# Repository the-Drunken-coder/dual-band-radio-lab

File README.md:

# Dual-Band Radio Lab

For the current evidence map, project boundaries and continuation state, see [project context](docs/project-context.md).

**Volunteer project:** Lane Araujo volunteered to take on this portable dual-band radio project. This repository documents the research and experiments.

## Vision

Explore a man-portable radio, roughly walkie-talkie-sized or slightly larger, with four persistent RF lanes:

- ~915 MHz LoRa
- ~915 MHz FLRC
- 2.4 GHz LoRa
- 2.4 GHz FLRC

The current architecture under evaluation gives each lane its own dedicated transceiver. Each radio normally listens continuously on its fixed network profile and may transmit on that same profile when commanded. The radios do not normally retune between bands or PHYs.

This removes the need for a separate fifth agile transmitter and also removes the requirement that all four lanes use the same radio family. Each lane can instead use hardware optimized for its own band, PHY, power, receiver performance, cost, and regulatory constraints.

The goal is to combine higher-bandwidth links with lower-rate, longer-range options for essential traffic, emergency communication, backup connectivity, and experimentation with automatic link selection. Relaying and automatic failover are possible future software features. This is the intended direction, not a demonstrated capability.

## Confirmed hardware requirements

- **U.S. operation:** Must be usable legally in the United States without an amateur-radio license.
- **Budget:** Up to $150 per complete node, with a stretch ceiling of $175.
- **Persistent receive coverage:** The node should normally monitor all four fixed network receive profiles at once rather than switching one receiver between bands or PHYs.
- **Fixed-role radios:** One transceiver is assigned to each band/PHY lane. A radio may switch between RX and TX, but does not normally change to another lane.
- **Transmission concurrency:** Simultaneous transmission on 915 MHz and 2.4 GHz is worth evaluating because the transmitters are independent. Same-band simultaneous TX/RX is not assumed to work and may require receiver blanking, filtering, protection, or additional isolation.
- **Portability:** Battery-powered and roughly walkie-talkie-sized or slightly larger. Exact dimensions, weight, and runtime are undecided.

Compute and USB/laptop connectivity remain undecided. An onboard single-board computer, such as a Raspberry Pi Zero, is an option rather than a requirement or an exclusion.

## Hardware direction

The architecture no longer requires every lane to use an LR2021. The earlier all-LR2021 design was attractive because one inexpensive chip could cover sub-GHz, 2.4 GHz, LoRa, and FLRC. With four fixed-role radios, that flexibility is no longer necessary.

Current candidate direction:

| Lane | Candidate hardware direction | Reason to investigate |
|---|---|---|
| ~915 MHz LoRa | high-power SX1262-based SPI module | mature sub-GHz LoRa hardware; 30 dBm / 1 W-capable modules exist |
| ~915 MHz FLRC | LR2021-based module | sub-GHz FLRC is an unusual LR2021 capability; high-power variants can also be evaluated |
| 2.4 GHz LoRa | high-power SX1280- or LR1121-based module | dedicated 2.4 GHz LoRa lane can prioritize link budget rather than multi-band flexibility |
| 2.4 GHz FLRC | high-power SX1280-based module or LR2021 | SX1280 is a mature 2.4 GHz FLRC/LoRa device and amplified modules exist |

These are candidates, not finalized purchases. Maximum module output power is a hardware capability, not an assumption that the maximum setting is legal for every LoRa or FLRC profile. Final frequencies, bandwidths, power, antenna gain, EIRP, and spectral limits must be validated for license-free U.S. operation before normal over-the-air testing.

When the four-lane prototype is justified, it may use four separate antennas, one per transceiver. This avoids the passive splitter loss and RF switching complexity of the earlier shared-antenna concept and makes each RF lane easier to characterize independently. Shared antennas, splitters, filters, LNAs, or duplexing can be reconsidered later if size or antenna count becomes more important.

See the [four-lane architecture](docs/dedicated-receiver-bank.md) for the long-term design and the [individual-radio test plan](docs/staged-rollout.md) for staged development of each radio.

## Develop one radio at a time

Each radio gets its own bring-up and characterization ladder: 2.4-LoRa, 2.4-FLRC, 915-LoRa and 915-FLRC. Test one lane in isolation with a compatible peer, progressing from a fixed-profile bench link through controlled tuning to its own operating envelope. Reuse a compatible SX1280 pair sequentially for the two 2.4 GHz PHYs if inventory confirms one. Combined-node and network work comes afterward.

The plan has explicit pass/stop and purchase gates. Board counts, exact variants and usable peers still need confirmation; candidates remain unselected. Do not order a full four-radio node or fabricate the [Rev A hardware](hardware/README.md) to characterize an individual radio. Its manufacturing hold remains in force.

## Optional LR2021 USB test carrier

The [dual-LR2021 USB test carrier](prototype/dual-lr2021-usb-carrier/README.md) is a separate development platform for laptop-driven radio experiments. It uses a USB-C ESP32-S3 controller and two socketed Core2021-HF-M modules. The archive includes editable KiCad files, pin maps, manufacturer evidence, validation reports, and a prototype fabrication package.

This carrier can test two chosen radio profiles at once. It does not provide the four persistent receive lanes or use the existing Rev A daughtercard interface. Firmware and the laptop test runner remain unimplemented. Physical fit, power, thermal behavior, and RF performance remain unverified.

Treat it as an optional design archive alongside the [individual-radio test plan](docs/staged-rollout.md). Its presence does not approve purchases or change the manufacturing hold on the existing [Rev A hardware](hardware/README.md).

## Example deployment

A person inside a house connects through a rooftop relay to a drone roughly one mile away. Every node normally keeps the four standardized receive profiles active. For outgoing traffic, the host selects the appropriate lane and that lane's transceiver temporarily changes from RX to TX.

A transmission on one band may require the other receiver on that same band to be blanked or protected from local transmitter leakage. Opposite-band receivers may be able to continue receiving during transmission, and simultaneous 915 MHz plus 2.4 GHz transmission is an experiment enabled by the independent radios rather than a guaranteed capability.

This is a scenario to test, not a confirmed range claim or a commitment to specific relaying or failover software. Terrain or obstructions could interrupt multiple links; 915 MHz is not assumed to guarantee coverage behind a hill.

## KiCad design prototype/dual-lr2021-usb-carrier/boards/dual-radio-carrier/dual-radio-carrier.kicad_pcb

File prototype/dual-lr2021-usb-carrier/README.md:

# Dual-LR2021 USB test carrier

A socketed, laptop-powered test platform for two Waveshare Core2021-HF-M radio modules. An ESP32-S3 controller handles the radios. The carrier replaces breadboard jumper wires with PCB traces and female sockets.

The intended workflow is to plug in USB-C, flash firmware from the laptop, command repeatable experiments, and collect machine-readable results. AI coding agents can use the same command-line tools as a person. The firmware and laptop test runner have not been implemented.

## Place in Dual-Band Radio Lab

This is an optional LR2021 development platform. It can help characterize individual LR2021 links and, later, interactions between two radios. Two copies provide two test nodes, each with two radios.

The project's [four-lane architecture](../../docs/dedicated-receiver-bank.md) requires four radios to monitor four persistent network profiles. This carrier holds two radios and can monitor two selected profiles at once. Changing their configuration between experiments does not provide four simultaneous listeners.

The existing [Rev A hardware](../../hardware/README.md) is a separate Pico 2 carrier with E22, Core2021, and E28 daughtercards. This ESP32 carrier uses direct Core2021 sockets. The controllers, GPIO maps, power arrangements, and card interfaces differ. The other daughtercards do not plug into this carrier.

The [individual-radio test plan](../../docs/staged-rollout.md) remains the development sequence. Existing-radio tests do not require this PCB. Adding this archive does not select LR2021 for every lane, approve purchases, or release the existing Rev A hardware for manufacturing.

## System

```mermaid
flowchart TD
    Host["Laptop: flash tools and future test runner"] -->|USB-C data| Bridge["Controller USB hub and CH343 serial bridge"]
    Bridge -->|UART and automatic BOOT/reset| MCU["ESP32-S3 firmware"]
    MCU -->|Shared SPI and separate CS, IRQ, BUSY, RESET| A["Core2021 radio A"]
    MCU -->|Shared SPI and separate CS, IRQ, BUSY, RESET| B["Core2021 radio B"]
    Host -->|USB power| Input["Controller USB supply and D1 diode"]
    Input --> LDO["Carrier 3.3 V radio regulator"]
    LDO --> A
    LDO --> B
    A --> AntA["Module antenna ports"]
    B --> AntB["Module antenna ports"]
```

Either radio can use a supported LoRa or FLRC profile at 915 MHz or 2.4 GHz. Firmware assigns each radio's role. One radio transmits or receives on its selected profile at a time. Nearby operation of both radios requires RF coupling and coexistence measurements.

The carrier routes digital signals and power. RF stays on the modules and their antenna connectors. There is no carrier RF switch, filter, or receiver-protection network. There is no battery input.

See [system responsibilities and intended software](SYSTEM.md) for the control flow, recovery behavior, and unfinished work.

## Hardware and files

The PCB is 100 x 75 mm, two layers, and 1.6 mm thick. Female sockets, the regulator, resistors, and capacitors are soldered to the carrier. The controller and radios plug in afterward.

| Item | Per carrier |
| --- | ---: |
| Waveshare ESP32-S3-DEV-KIT-N8R8-M, SKU 24243 | 1 |
| Waveshare Core2021-HF-M, SKU 34523 | 2 |
| Samtec SSW-122-01-G-S controller sockets | 2 |
| Samtec SSW-108-01-G-S radio sockets | 4 |
| TI TLV1117LV33DCYR radio regulator | 1 |

The [BOM](boards/dual-radio-carrier/bom.csv) includes the remaining parts and separately purchased plug-in modules. Antennas, USB cables, and mounting hardware are not included. Use the exact selected module variants and check their supplied male headers against socket samples.

- [Editable KiCad project](boards/dual-radio-carrier/dual-radio-carrier.kicad_pro), [PCB](boards/dual-radio-carrier/dual-radio-carrier.kicad_pcb), and [schematic](boards/dual-radio-carrier/dual-radio-carrier.kicad_sch).
- [Assembly, GPIO, power, and rebuild instructions](boards/dual-radio-carrier/README.md).
- [GPIO map](boards/dual-radio-carrier/gpio-map.csv) and [radio socket map](boards/dual-radio-carrier/radio-socket-map.csv).
- [Native KiCad check summary](boards/dual-radio-carrier/build/native-summary.json) and [saved-file geometry checks](boards/dual-radio-carrier/build/verification.json).
- [Archived manufacturer evidence](extra/references/) and [historical independent review](extra/reviews/electrical-review.md).
- [Prototype Gerber, drill, BOM, and placement package](mfg/dual-radio-carrier-rev-a-prototype.zip), with [source and output hashes](mfg/dual-radio-carrier-rev-a-prototype/manifest.json).

## Validation and manufacturing status

Native KiCad 10.99.0 checks passed on the saved files: zero ERC violations, zero DRC violations, zero unconnected items, and zero schematic parity issues. The separate saved-file checker also passed. Report hashes identify the exact PCB and schematic in this archive.

No physical board has been fabricated, assembled, or tested. These results do not establish socket fit, USB power capacity, temperature, flashing reliability, or RF performance. The controller's external header current allowance is not specified by its manufacturer. The radio regulator's rating does not establish the upstream USB or diode capacity.

The manufacturing files are an engineering-prototype snapshot for review, not evidence of manufacturing approval or supplier acceptance. No quote, order, manufacturer upload, or purchase has been made. The generic BOM includes plug-in modules, while placement data contains only carrier-mounted parts. A factory assembly handoff must separate those items and confirm part sourcing, through-hole assembly, orientation, and coordinate conventions with the chosen supplier.

The first assembled units need sample-fit, power, thermal, USB recovery, and controlled radio tests. Keep the project's existing manufacturing hold and staged purchase decisions separate from this archive.

## Working with this snapshot

Open the KiCad project inside `boards/dual-radio-carrier/`. The checked board uses the native file format saved by Backplane KiCad 10.99.0. Do not assume older stable KiCad releases can open it.

Run the existing rebuild instructions from this directory:

```sh
cd prototype/dual-lr2021-usb-carrier
```

Generators can overwrite manual CAD edits. Preserve the included final PCB and schematic before regeneration. The saved native CAD files are the uploaded design, and the build reports apply only while their hashes match.

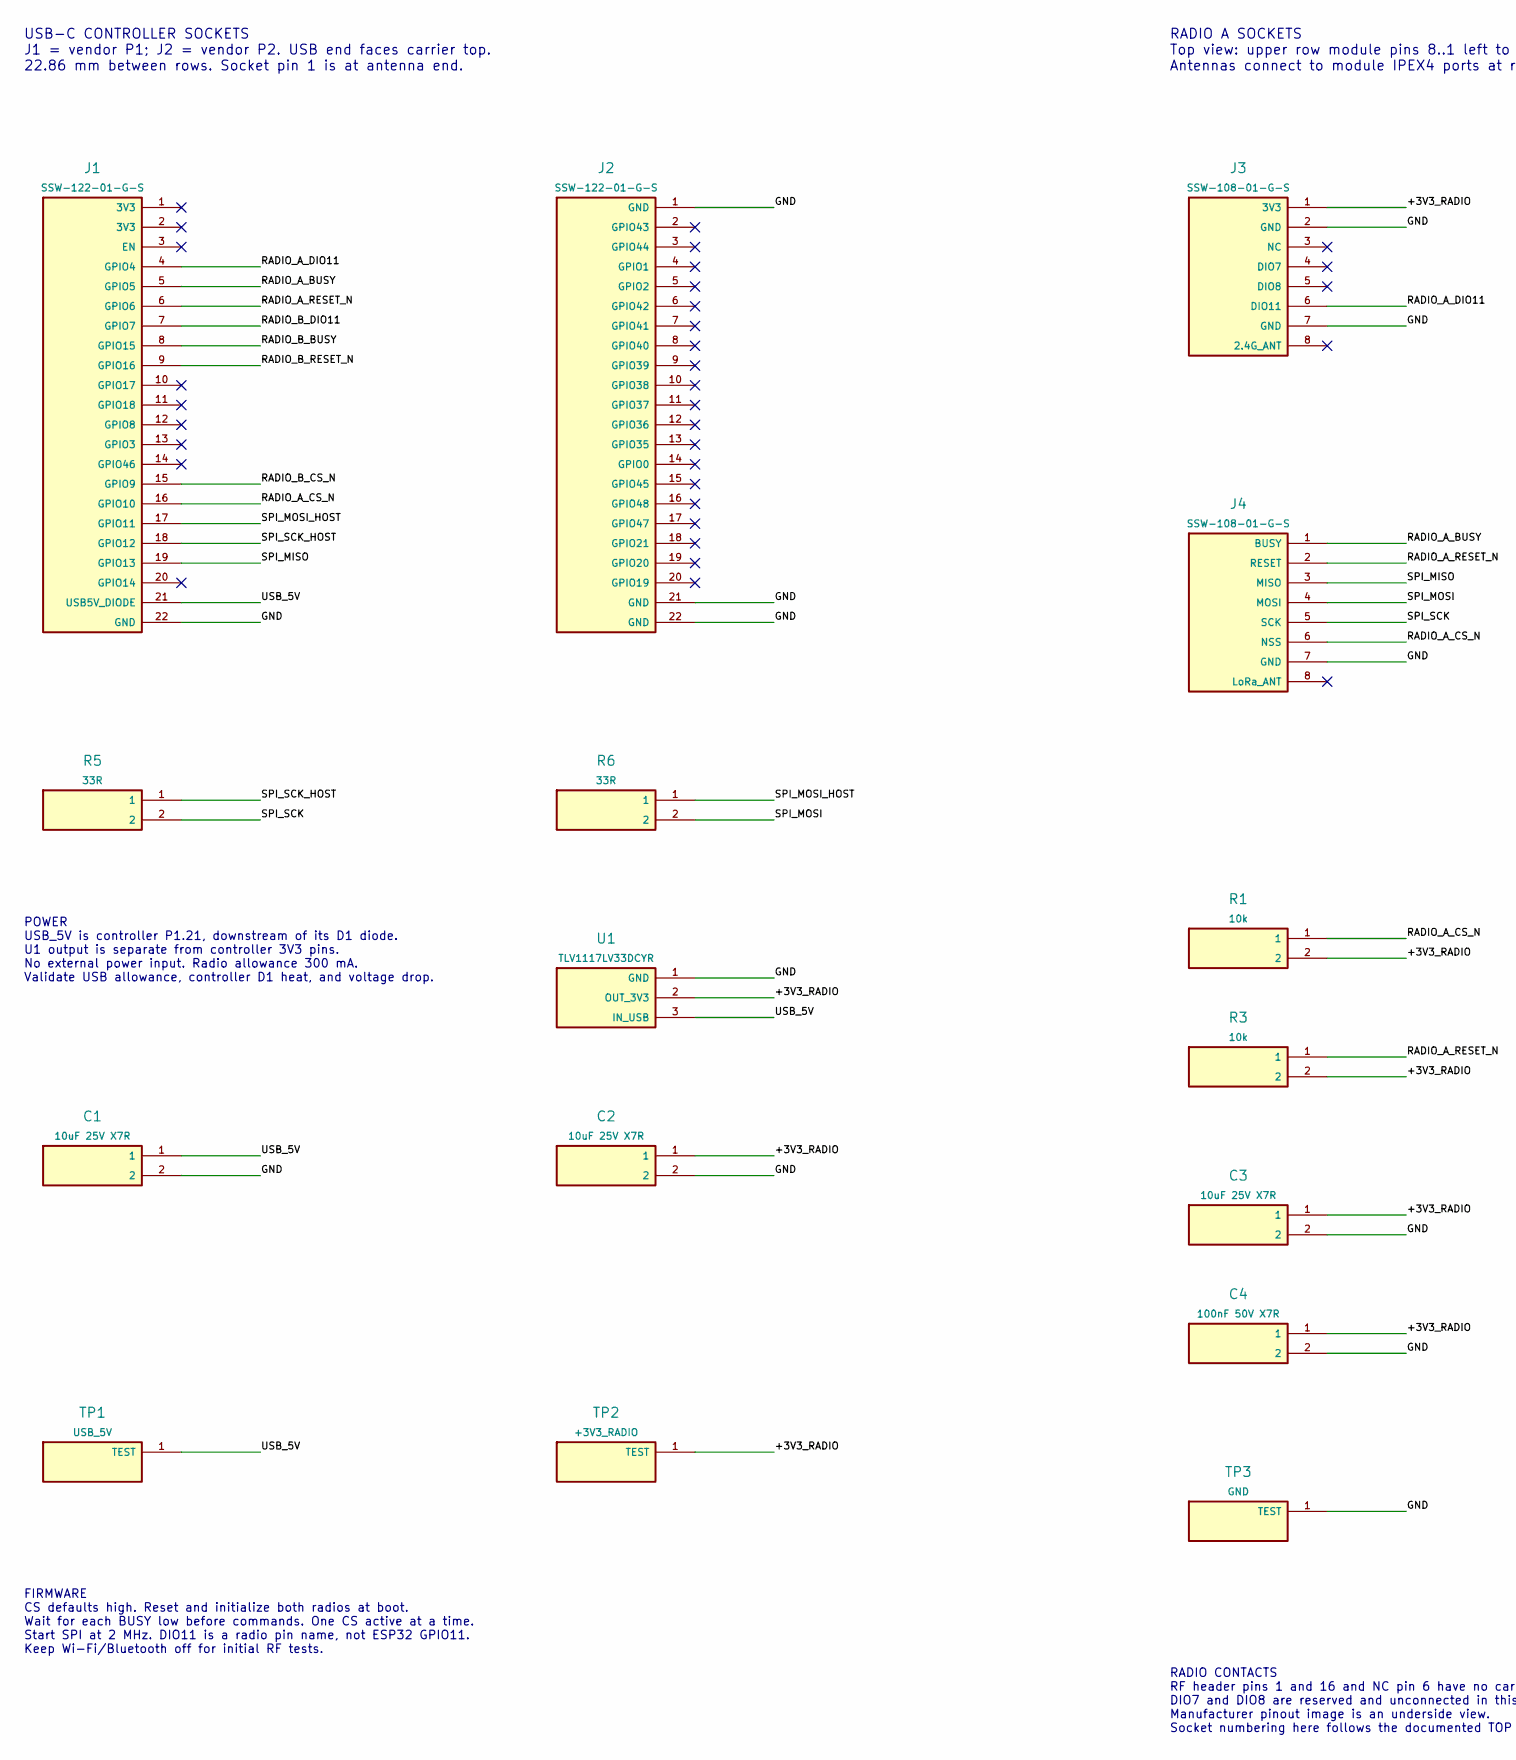
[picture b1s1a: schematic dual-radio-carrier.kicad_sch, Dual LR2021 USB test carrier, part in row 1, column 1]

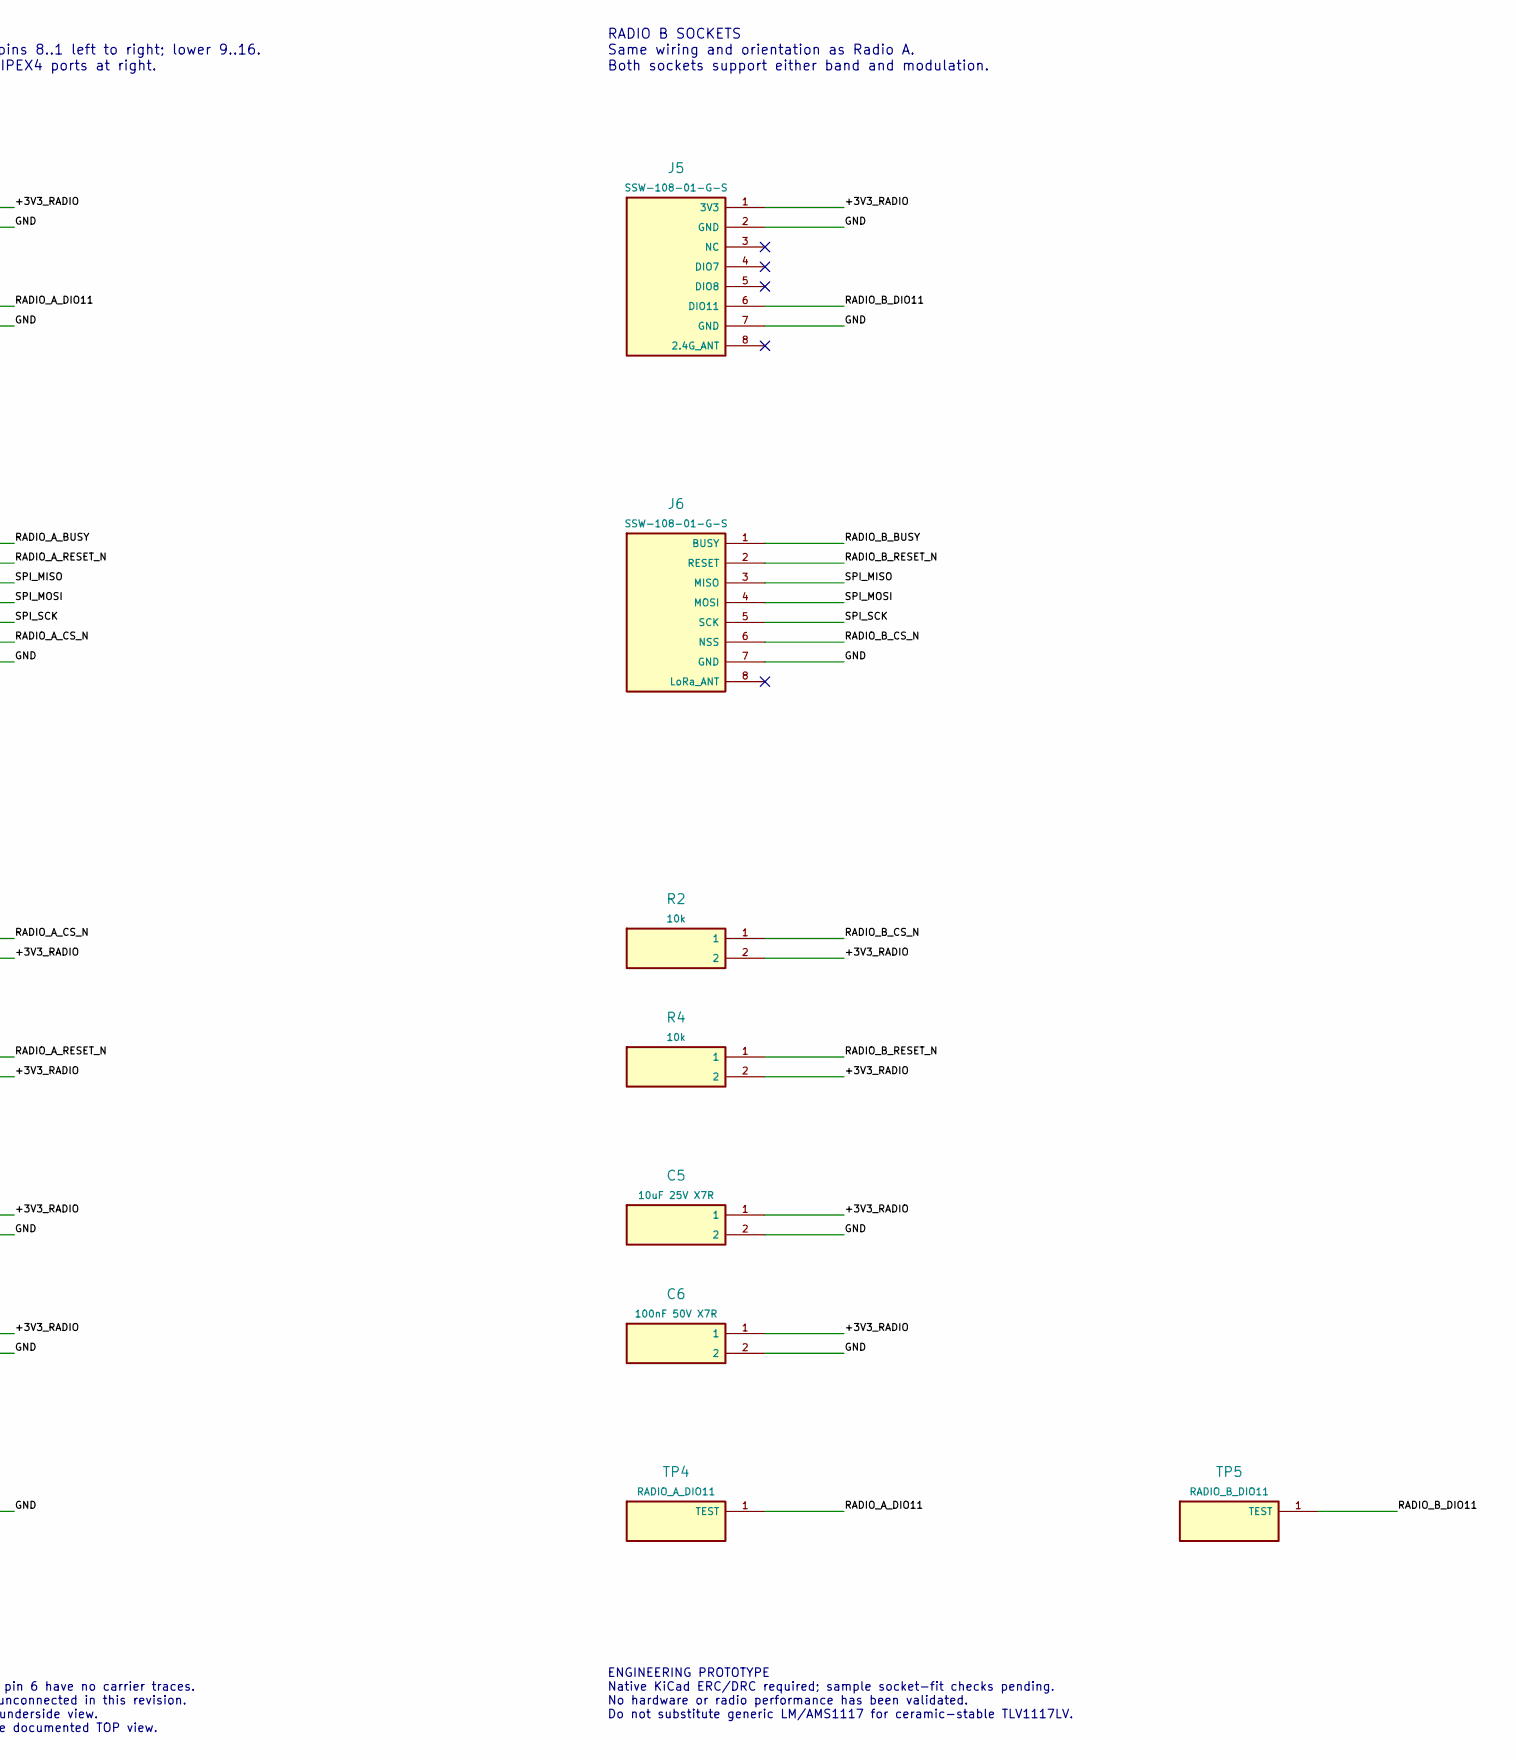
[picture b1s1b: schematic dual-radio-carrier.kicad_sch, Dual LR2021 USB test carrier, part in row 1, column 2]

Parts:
C1, C2, C3, C5: 10uF 25V X7R; C_1206; MPN C1206C106K3RACTU
C4, C6: 100nF 50V X7R; C_0805; MPN C0805C104K5RACTU
J1, J2: SSW-122-01-G-S; Socket_1x22_P2.54_USB_Top; MPN SSW-122-01-G-S
J3: SSW-108-01-G-S; Socket_1x08_P2.54_Horizontal_SolidGND2; MPN SSW-108-01-G-S
J4, J5, J6: SSW-108-01-G-S; Socket_1x08_P2.54_Horizontal; MPN SSW-108-01-G-S
R1, R2, R3, R4: 10k; R_0805; MPN RC0805FR-0710KL
R5, R6: 33R; R_0805; MPN RC0805FR-0733RL
TP1: USB_5V; TestPoint_1.5mm; MPN PCB copper test pad
TP2: +3V3_RADIO; TestPoint_1.5mm; MPN PCB copper test pad
TP3: GND; TestPoint_1.5mm; MPN PCB copper test pad
TP4: RADIO_A_DIO11; TestPoint_1.5mm; MPN PCB copper test pad
TP5: RADIO_B_DIO11; TestPoint_1.5mm; MPN PCB copper test pad
U1: TLV1117LV33DCYR; SOT223_TabPin2; MPN TLV1117LV33DCYR

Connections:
/+3V3_RADIO: C2.1, C3.1, C4.1, C5.1, C6.1, J3.1 (3V3), J5.1 (3V3), R1.2, R2.2, R3.2, R4.2, TP2.1, U1.2 (OUT_3V3)
/GND: C1.2, C2.2, C3.2, C4.2, C5.2, C6.2, J1.22 (GND), J2.1 (GND), J2.21 (GND), J2.22 (GND), J3.2 (GND), J3.7 (GND), J4.7 (GND), J5.2 (GND), J5.7 (GND), J6.7 (GND), TP3.1, U1.1 (GND)
/RADIO_A_BUSY: J1.5 (GPIO5), J4.1 (BUSY)
/RADIO_A_CS_N: J1.16 (GPIO10), J4.6 (NSS), R1.1
/RADIO_A_DIO11: J1.4 (GPIO4), J3.6 (DIO11), TP4.1
/RADIO_A_RESET_N: J1.6 (GPIO6), J4.2 (RESET), R3.1
/RADIO_B_BUSY: J1.8 (GPIO15), J6.1 (BUSY)
/RADIO_B_CS_N: J1.15 (GPIO9), J6.6 (NSS), R2.1
/RADIO_B_DIO11: J1.7 (GPIO7), J5.6 (DIO11), TP5.1
/RADIO_B_RESET_N: J1.9 (GPIO16), J6.2 (RESET), R4.1
/SPI_MISO: J1.19 (GPIO13), J4.3 (MISO), J6.3 (MISO)
/SPI_MOSI: J4.4 (MOSI), J6.4 (MOSI), R6.2
/SPI_MOSI_HOST: J1.17 (GPIO11), R6.1
/SPI_SCK: J4.5 (SCK), J6.5 (SCK), R5.2
/SPI_SCK_HOST: J1.18 (GPIO12), R5.1
/USB_5V: C1.1, J1.21 (USB5V_DIODE), TP1.1, U1.3 (IN_USB)

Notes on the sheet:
USB-C CONTROLLER SOCKETS J1 = vendor P1; J2 = vendor P2. USB end faces carrier top. 22.86 mm between rows. Socket pin 1 is at antenna end.
RADIO A SOCKETS Top view: upper row module pins 8..1 left to right; lower 9..16. Antennas connect to module IPEX4 ports at right.
RADIO B SOCKETS Same wiring and orientation as Radio A. Both sockets support either band and modulation.
POWER USB_5V is controller P1.21, downstream of its D1 diode. U1 output is separate from controller 3V3 pins. No external power input. Radio allowance 300 mA. Validate USB allowance, controller D1 heat, and voltage drop.
FIRMWARE CS defaults high. Reset and initialize both radios at boot. Wait for each BUSY low before commands. One CS active at a time. Start SPI at 2 MHz. DIO11 is a radio pin name, not ESP32 GPIO11. Keep Wi-Fi/Bluetooth off for initial RF tests.
RADIO CONTACTS RF header pins 1 and 16 and NC pin 6 have no carrier traces. DIO7 and DIO8 are reserved and unconnected in this revision. Manufacturer pinout image is an underside view. Socket numbering here follows the documented TOP view.
ENGINEERING PROTOTYPE Native KiCad ERC/DRC required; sample socket-fit checks pending. No hardware or radio performance has been validated. Do not substitute generic LM/AMS1117 for ceramic-stable TLV1117LV.

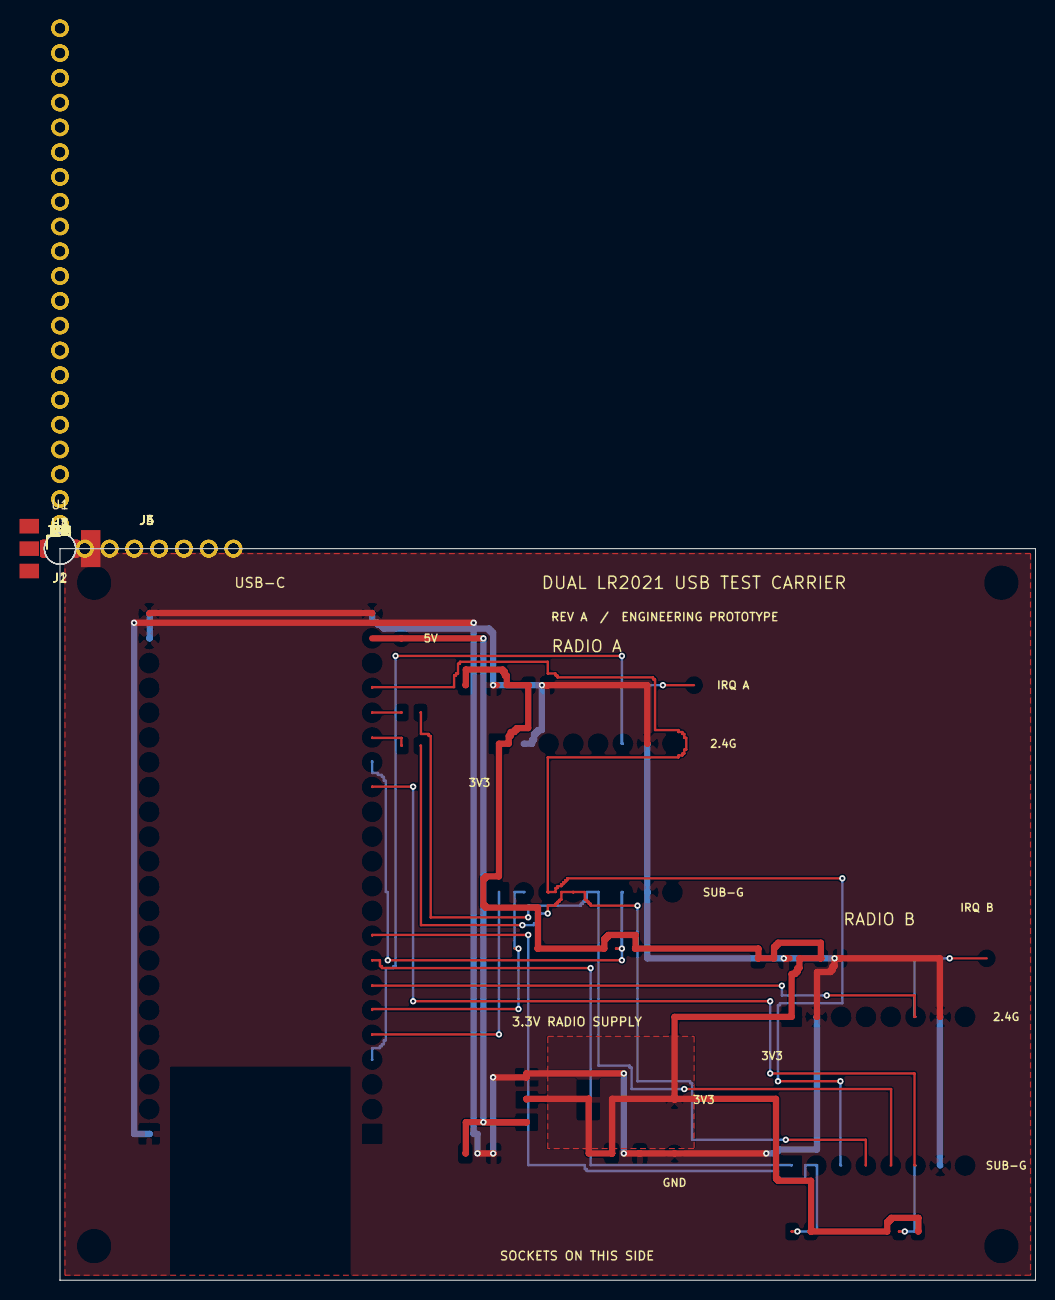
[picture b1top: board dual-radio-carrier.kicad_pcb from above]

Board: 2 copper layers, 100.0 x 75.0 mm, 28 parts (0 on the bottom side), 16 nets.

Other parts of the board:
H1, H2, H3, H4: M3 NPTH; MountingHole_3.2mm

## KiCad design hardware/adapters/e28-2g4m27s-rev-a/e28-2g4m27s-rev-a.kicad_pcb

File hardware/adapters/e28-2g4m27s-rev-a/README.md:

# e28-2g4m27s-rev-a

Editable Rev A schematic, routed PCB, selected BOM and schematic PDF. Native KiCad ERC and DRC pass with zero findings, including schematic parity. Two layers, 2 oz copper per side. Review only; no manufacturing release.

Open [e28-2g4m27s-rev-a.kicad_pcb](e28-2g4m27s-rev-a.kicad_pcb) in KiCad. The final native board is authoritative; do not overwrite it with the intermediate router session. See the hardware DESIGN_REVIEW.md, POWER_BUDGET.md and ASSEMBLY_NOTES.md for access, route lengths, power estimates and later physical acceptance.

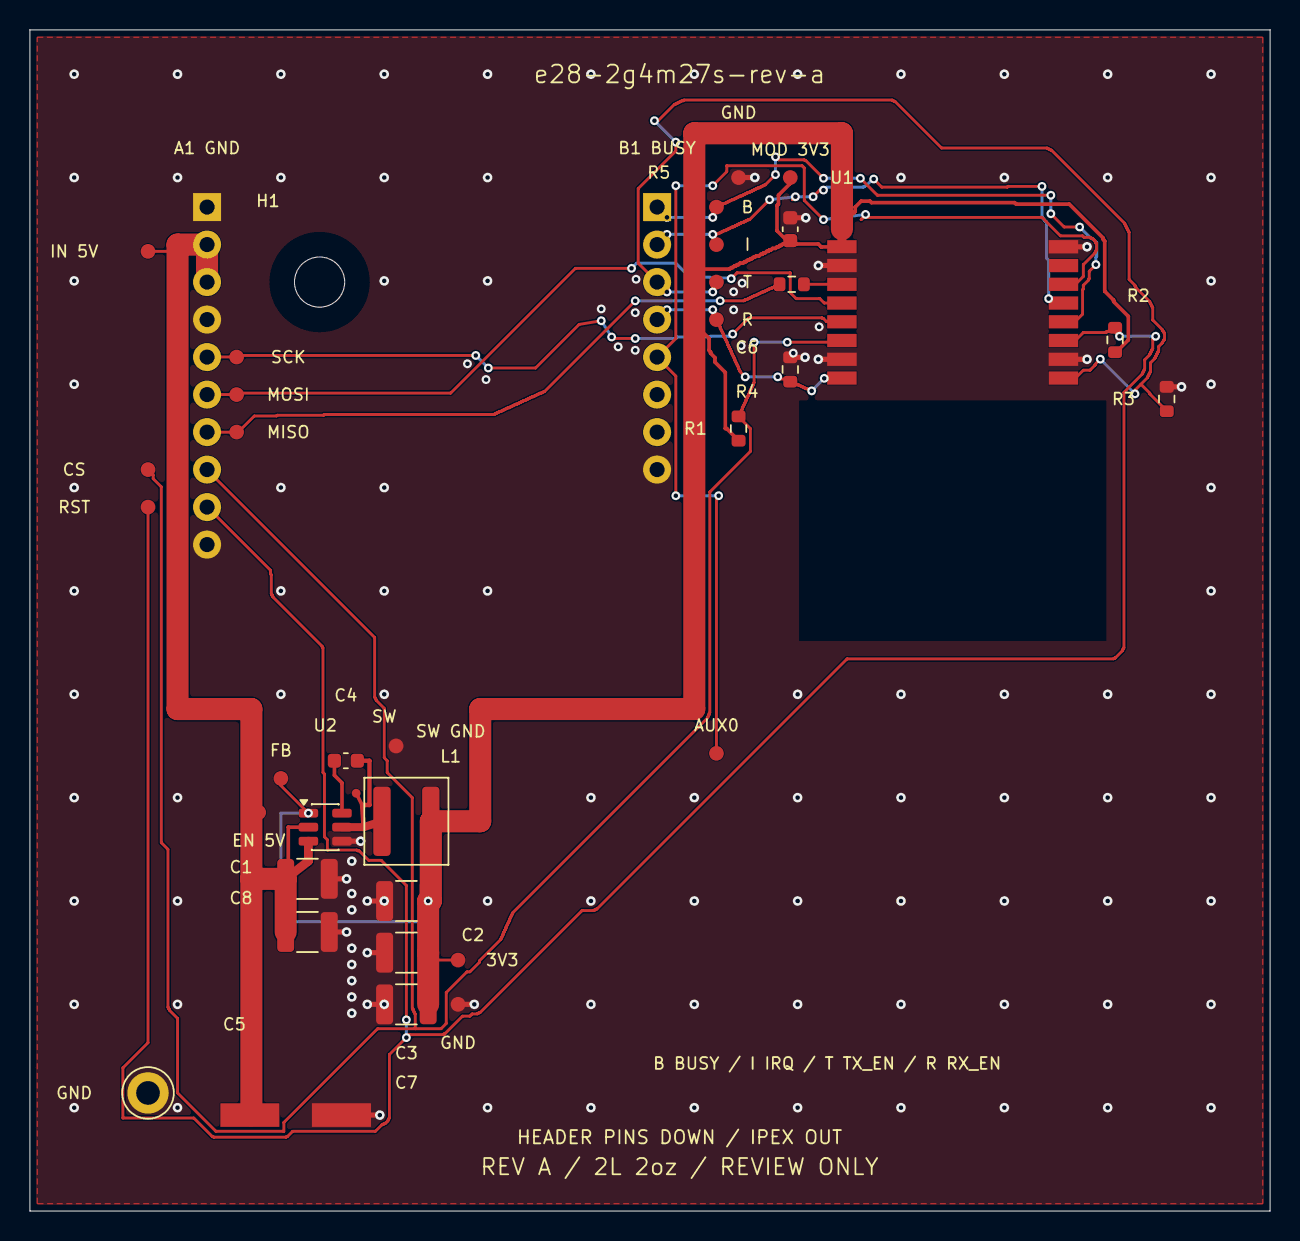
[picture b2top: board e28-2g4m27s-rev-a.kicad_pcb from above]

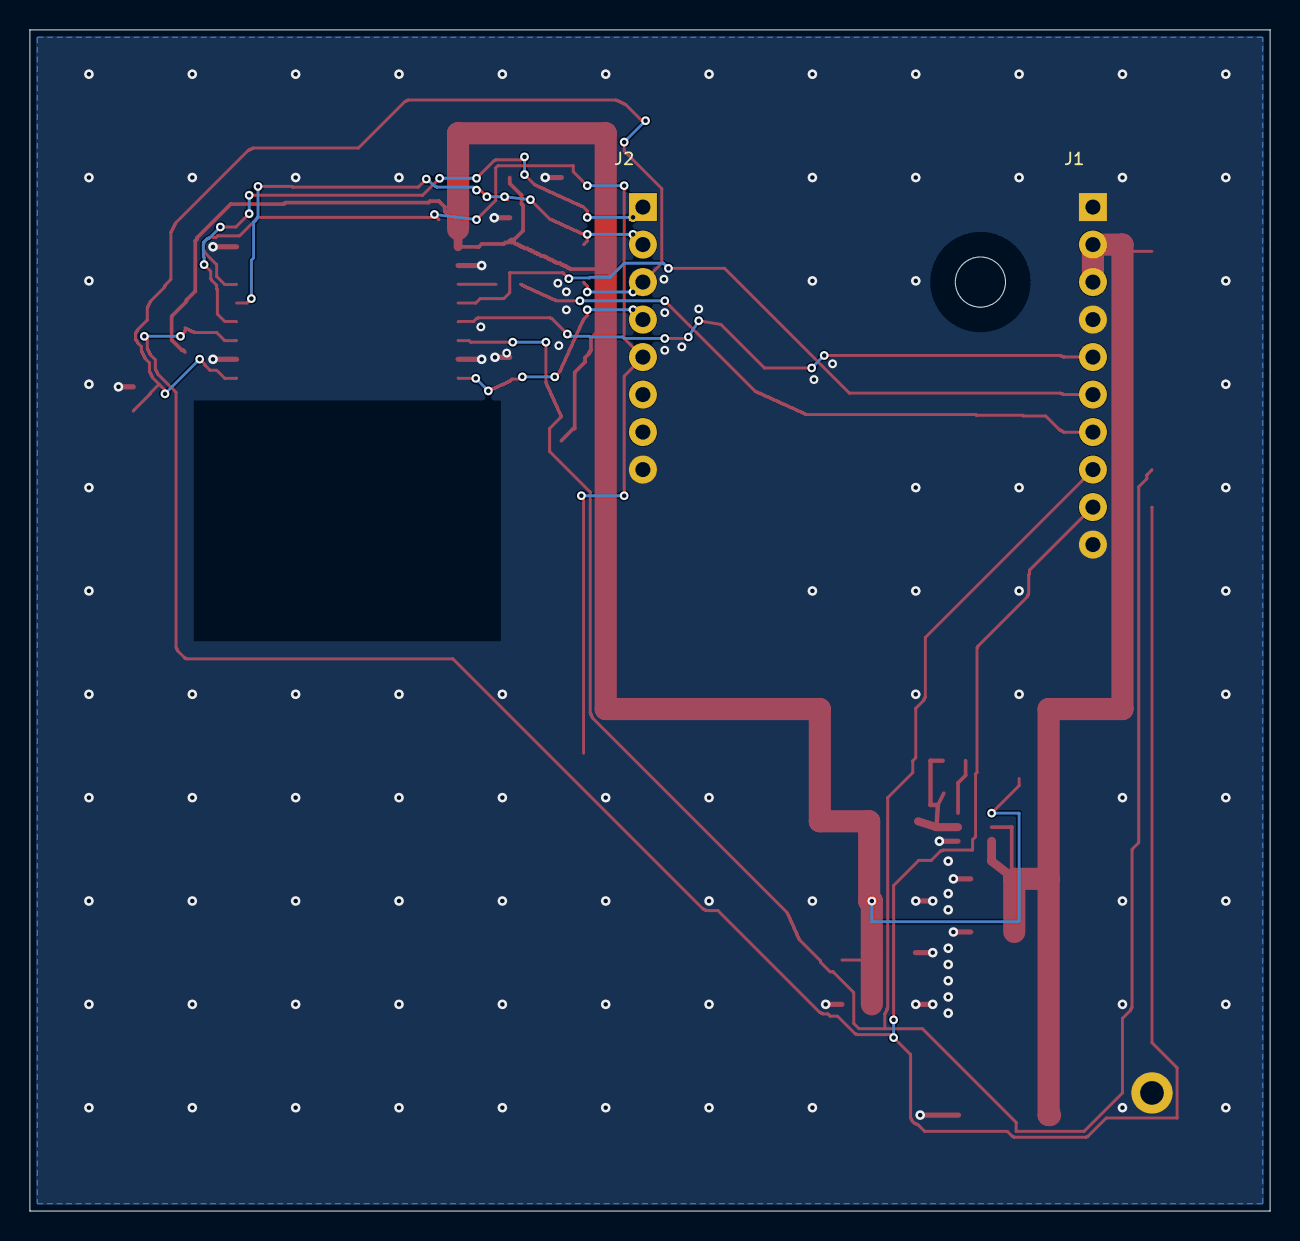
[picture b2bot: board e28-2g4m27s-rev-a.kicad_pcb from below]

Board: 2 copper layers, 84.0 x 80.0 mm, 39 parts (2 on the bottom side), 16 nets.

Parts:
C1, C2, C3, C7, C8: 22uF; C_1210_3225Metric
C4, C6: 100nF; C_0603_1608Metric
C5: 220uF; Panasonic_FK_E_8x6.2
H1: M3 alignment hole; Alignment_M3_3.4mm
J1: TSW-110-07-G-S; TSW_1x10
J2: TSW-108-07-G-S; TSW_1x8
L1: 4.7uH; L_Coilcraft_XAL5030-XXX
R1, R2, R3, R4: 10k; R_0603_1608Metric
R5: 22; R_0603_1608Metric
TP1: SPI_SCK; Probe_Pad_D1.0mm
TP2: SPI_MOSI; Probe_Pad_D1.0mm
TP3: SPI_MISO; Probe_Pad_D1.0mm
TP4: CS_N; Probe_Pad_D1.0mm
TP5: RESET_N; Probe_Pad_D1.0mm
TP6: BUSY; Probe_Pad_D1.0mm
TP7: IRQ; Probe_Pad_D1.0mm
TP8: TX_EN; Probe_Pad_D1.0mm
TP9: RX_EN; Probe_Pad_D1.0mm
TP10: IN_5V; Probe_Pad_D1.0mm
TP11: CLIP_GND; TestPoint_Keystone_5010-5014_Multipurpose
TP12: AUX0; Probe_Pad_D1.0mm
TP13: OUT_3V3; Probe_Pad_D1.0mm
TP14: REG_GND; Probe_Pad_D1.0mm
TP15: EN_5V; Probe_Pad_D1.0mm
TP16: SW; Probe_Pad_D0.6mm
TP17: FB; Probe_Pad_D1.0mm
TP18: MOD_3V3; Probe_Pad_D1.0mm
TP19: MOD_GND; Probe_Pad_D1.0mm
TP20: SW_GND; Probe_Pad_D1.0mm
U1: E28-2G4M27S; E28_2G4M27S
U2: AP63203WU-7; TSOT-23-6

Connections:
/AUX0: J2.5, TP12.1, U1.14
/BST: C4.1, U2.6
/BUSY: J2.1, TP6.1, U1.12
/CS_N: J1.8, R1.2, TP4.1, U1.6
/GND: C1.2, C2.2, C3.2, C5.2, C6.2, C7.2, C8.2, J1.1, J1.4, J1.10, J2.8, R3.2, R4.2, TP11.1, TP14.1, TP19.1, TP20.1, U1.2, U1.7, U1.10, U1.16, U2.4
/IRQ: J2.2, TP7.1, U1.13
/RADIO_3V3: C2.1, C3.1, C6.1, C7.1, L1.2, R1.1, R2.1, TP13.1, TP17.1, TP18.1, U1.1, U2.1
/RESET_N: J1.9, R2.2, TP5.1, U1.11
/RX_EN: J2.4, R4.1, TP9.1, U1.8
/SLOT_5V: C1.1, C5.1, C8.1, J1.2, J1.3, TP10.1, TP15.1, U2.2, U2.3
/SPI_MISO: J1.7, R5.2, TP3.1
/SPI_MISO_SRC: R5.1, U1.3
/SPI_MOSI: J1.6, TP2.1, U1.4
/SPI_SCK: J1.5, TP1.1, U1.5
/SW: C4.2, L1.1, TP16.1, U2.5
/TX_EN: J2.3, R3.1, TP8.1, U1.9

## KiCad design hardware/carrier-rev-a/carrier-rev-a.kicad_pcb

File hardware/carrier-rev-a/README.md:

# carrier-rev-a

Editable Rev A schematic, routed PCB, selected BOM and schematic PDF. Native KiCad ERC and DRC pass with zero findings, including schematic parity. Two layers, 2 oz copper per side. Review only; no manufacturing release.

Open [carrier-rev-a.kicad_pcb](carrier-rev-a.kicad_pcb) in KiCad. The final native board is authoritative; do not overwrite it with the intermediate router session. See the hardware DESIGN_REVIEW.md, POWER_BUDGET.md and ASSEMBLY_NOTES.md for access, route lengths, power estimates and later physical acceptance.

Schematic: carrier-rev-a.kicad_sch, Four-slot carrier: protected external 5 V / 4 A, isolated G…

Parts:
C1: 10nF; C_0603_1608Metric; MPN GRM188R71H103KA01D
C2: 1uF; C_0805_2012Metric; MPN GRM21BR71C105KA01L
C3: 220uF; Panasonic_FK_E_8x6.2; MPN EEEFK1A221P
C4, C5: 22uF; C_1210_3225Metric; MPN C3225X7R1E226M250AB
C6, C7, C8, C9, C10, C11, C12: 100nF; C_0603_1608Metric; MPN GRM188R71H104KA93D
H1, H2, H3, H4: Captive M3 x 25 alignment post; Alignment_M3_3.4mm; MPN SSCF-M3-25-A2
J1, J3, J5, J7: SSQ-110-01-G-S; SSQ_1x10; MPN SSQ-110-01-G-S
J2, J4, J6, J8: SSQ-108-01-G-S; SSQ_1x8; MPN SSQ-108-01-G-S
J9: 5 V / 4 A INPUT; PhoenixContact_MSTBA_2,5_2-G-5,08_1x02_P5.08mm_Horizontal; MPN 1757242
J10, J11: SSQ-120-01-G-S; SSQ_1x20; MPN SSQ-120-01-G-S
MP1, MP2, MP3, MP4: M3 captive-post clamp nut; MPN HPN-M3-A2
MP5: External cable mating plug; MPN 1757019
Q1: DMG2305UX-7; SOT-23; MPN DMG2305UX-7
R1: 267k; R_0603_1608Metric; MPN RC0603FR-07267KL
R2, R7, R10: 100k; R_0603_1608Metric; MPN RC0603FR-07100KL
R3: 340k 0.1%; R_0603_1608Metric; MPN RT0603BRD07340KL
R4: 100k 0.1%; R_0603_1608Metric; MPN RT0603BRD07100KL
R5: 715; R_0603_1608Metric; MPN RC0603FR-07715RL
R6, R8, R9, R13, R14, R15, R16, R17, R18: 10k; R_0603_1608Metric; MPN RC0603FR-0710KL
R11, R12: 1k; R_0603_1608Metric; MPN RC0603FR-071KL
R19: 100; R_0603_1608Metric; MPN RC0603FR-07100RL
R20, R21, R22: 22; R_0603_1608Metric; MPN RC0603FR-0722RL
TP1: S1_5V; Probe_Pad_D1.0mm; MPN PCB-PROBE-PAD
TP2: S1_CS_N; Probe_Pad_D1.0mm; MPN PCB-PROBE-PAD
TP3: S1_BUSY; Probe_Pad_D1.0mm; MPN PCB-PROBE-PAD
TP4: S1_IRQ; Probe_Pad_D1.0mm; MPN PCB-PROBE-PAD
TP5: S1_RESET_N; Probe_Pad_D1.0mm; MPN PCB-PROBE-PAD
TP6: S1_TX_EN; Probe_Pad_D1.0mm; MPN PCB-PROBE-PAD
TP7: S1_RX_EN; Probe_Pad_D1.0mm; MPN PCB-PROBE-PAD
TP8: S1_GND; TestPoint_Keystone_5010-5014_Multipurpose; MPN 5011
TP9: S2_5V; Probe_Pad_D1.0mm; MPN PCB-PROBE-PAD
TP10: S2_CS_N; Probe_Pad_D1.0mm; MPN PCB-PROBE-PAD
TP11: S2_BUSY; Probe_Pad_D1.0mm; MPN PCB-PROBE-PAD
TP12: S2_IRQ; Probe_Pad_D1.0mm; MPN PCB-PROBE-PAD
TP13: S2_RESET_N; Probe_Pad_D1.0mm; MPN PCB-PROBE-PAD
TP14: S2_GND; TestPoint_Keystone_5010-5014_Multipurpose; MPN 5011
TP15: S3_5V; Probe_Pad_D1.0mm; MPN PCB-PROBE-PAD
TP16: S3_CS_N; Probe_Pad_D1.0mm; MPN PCB-PROBE-PAD
TP17: S3_BUSY; Probe_Pad_D1.0mm; MPN PCB-PROBE-PAD
TP18: S3_IRQ; Probe_Pad_D1.0mm; MPN PCB-PROBE-PAD
TP19: S3_RESET_N; Probe_Pad_D1.0mm; MPN PCB-PROBE-PAD
TP20: S3_TX_EN; Probe_Pad_D1.0mm; MPN PCB-PROBE-PAD
TP21: S3_RX_EN; Probe_Pad_D1.0mm; MPN PCB-PROBE-PAD
TP22: S3_GND; TestPoint_Keystone_5010-5014_Multipurpose; MPN 5011
TP23: S4_5V; Probe_Pad_D1.0mm; MPN PCB-PROBE-PAD
TP24: S4_CS_N; Probe_Pad_D1.0mm; MPN PCB-PROBE-PAD
TP25: S4_BUSY; Probe_Pad_D1.0mm; MPN PCB-PROBE-PAD
TP26: S4_IRQ; Probe_Pad_D1.0mm; MPN PCB-PROBE-PAD
TP27: S4_RESET_N; Probe_Pad_D1.0mm; MPN PCB-PROBE-PAD
TP28: S4_TX_EN; Probe_Pad_D1.0mm; MPN PCB-PROBE-PAD
TP29: S4_RX_EN; Probe_Pad_D1.0mm; MPN PCB-PROBE-PAD
TP30: S4_GND; TestPoint_Keystone_5010-5014_Multipurpose; MPN 5011
TP31: IN_5V; Probe_Pad_D1.0mm; MPN PCB-PROBE-PAD
TP32: BUS_5V; Probe_Pad_D1.0mm; MPN PCB-PROBE-PAD
TP33: VBUS; Probe_Pad_D1.0mm; MPN PCB-PROBE-PAD
TP34: VSYS; Probe_Pad_D1.0mm; MPN PCB-PROBE-PAD
TP35: PICO_3V3; Probe_Pad_D1.0mm; MPN PCB-PROBE-PAD
TP36: IOREF_3V3; Probe_Pad_D1.0mm; MPN PCB-PROBE-PAD
TP37: UVLO; Probe_Pad_D1.0mm; MPN PCB-PROBE-PAD
TP38: OVLO; Probe_Pad_D1.0mm; MPN PCB-PROBE-PAD
TP39: DVDT; Probe_Pad_D1.0mm; MPN PCB-PROBE-PAD
TP40: ILIM; Probe_Pad_D1.0mm; MPN PCB-PROBE-PAD
TP41: EXP_CS; Probe_Pad_D1.0mm; MPN PCB-PROBE-PAD
TP42: EXP_RST; Probe_Pad_D1.0mm; MPN PCB-PROBE-PAD
TP43: OE_N; Probe_Pad_D1.0mm; MPN PCB-PROBE-PAD
TP44: P_SCK; Probe_Pad_D1.0mm; MPN PCB-PROBE-PAD
TP45: P_MOSI; Probe_Pad_D1.0mm; MPN PCB-PROBE-PAD
TP46: P_MISO; Probe_Pad_D1.0mm; MPN PCB-PROBE-PAD
TP47: SCK; Probe_Pad_D1.0mm; MPN PCB-PROBE-PAD
TP48: MOSI; Probe_Pad_D1.0mm; MPN PCB-PROBE-PAD
TP49: MISO; Probe_Pad_D1.0mm; MPN PCB-PROBE-PAD
TP50: ENTRY_GND; TestPoint_Keystone_5010-5014_Multipurpose; MPN 5011
TP51: U3_GND; Probe_Pad_D1.0mm; MPN PCB-PROBE-PAD
U1: Pico 2 with headers, SC1632; MPN SC1632
U2: TPS259470LRPWR; TPS25947_RPW0010A; MPN TPS259470LRPWR
U3: AP2112K-3.3TRG1; SOT-23-5; MPN AP2112K-3.3TRG1
U4: MCP23S17-E/SO; SOIC-28W_7.5x17.9mm_P1.27mm; MPN MCP23S17-E/SO
U5, U6: SN74LVC8T245PWR; TSSOP-24_4.4x7.8mm_P0.65mm; MPN SN74LVC8T245PWR
U7: SN74LVC1T45DBVR; SOT-23-6; MPN SN74LVC1T45DBVR

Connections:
/DVDT: R19.1, TP39.1, U2.7 (DVDT)
/DVDT_C: C1.1, R19.2
/EXP_CS_N: R9.2, TP41.1, U4.11 (CS_N), U5.15 (B7)
/EXP_MISO_SRC: R22.1, U4.14 (SO)
/EXP_RESET_N: R8.1, TP42.1, U4.18 (RESET_N), U5.14 (B8)
/EXT_5V: C2.1, J9.1, R1.1, R3.1, TP31.1, U2.5 (IN)
/GND: C1.2, C2.2, C3.2 (-), C4.2, C5.2, C6.2, C7.2, C8.2, C9.2, C10.2, C11.2, C12.2, J1.1, J1.4, J1.10, J2.8, J3.1, J3.4, J3.10, J4.8, J5.1, J5.4, J5.10, J6.8, J7.1, J7.4, J7.10, J8.8, J9.2, J10.3, J10.8, J10.13, J10.18, J11.3, J11.8, J11.13, J11.18, R2.2, R4.2, R5.2, R7.2, R8.2, R10.2, R11.2, R12.2, R13.2, TP8.1, TP14.1, TP22.1, TP30.1, TP50.1, TP51.1, U1.3 (GND), U1.8 (GND), U1.13 (GND), U1.18 (GND), U1.23 (GND), U1.28 (GND), U1.33 (AGND), U1.38 (GND), U2.8 (GND), U3.2 (GND), U4.10 (VSS), U4.15 (A0), U4.16 (A1), U4.17 (A2), U5.11 (GND), U5.12 (GND), U5.13 (GND), U6.2 (DIR), U6.11 (GND), U6.12 (GND), U6.13 (GND), U7.2 (GND), U7.5 (DIR)
/ILIM: R5.1, TP40.1, U2.9 (ILM)
/IOREF_3V3: C5.1, C6.1, C8.1, C10.1, C12.1, J2.7, J4.7, J6.7, J8.7, R9.1, R12.1, TP36.1, U3.5 (VOUT), U4.9 (VDD), U5.23 (VCCB), U5.24 (VCCB), U6.23 (VCCB), U6.24 (VCCB), U7.6 (VCCB)
/OVLO: R3.2, R4.1, TP38.1, U2.2 (OVLO)
/PICO_3V3: C7.1, C9.1, C11.1, J11.16, R6.1, R14.1, R15.1, R16.1, R17.1, R18.1, TP35.1, U1.36 (3V3_OUT), U5.1 (VCCA), U5.2 (DIR), U6.1 (VCCA), U7.1 (VCCA)
/PICO_VSYS: J11.19, Q1.2 (S), TP34.1, U1.39 (VSYS)
/P_EXP_CS_N: J10.20, R18.2, U1.20 (GP15), U5.9 (A7)
/P_EXP_RESET_N: J11.1, R13.1, U1.21 (GP16), U5.10 (A8)
/P_IO_OE_N: J11.2, R6.2, TP43.1, U1.22 (GP17), U5.22 (OE_N), U6.22 (OE_N)
/P_S1_BUSY: J10.2, U1.2 (GP1), U6.3 (A1)
/P_S1_CS_N: J10.7, R14.2, U1.7 (GP5), U5.5 (A3)
/P_S1_IRQ: J10.1, U1.1 (GP0), U6.4 (A2)
/P_S2_BUSY: J10.5, U1.5 (GP3), U6.5 (A3)
/P_S2_CS_N: J10.16, R15.2, U1.16 (GP12), U5.6 (A4)
/P_S2_IRQ: J10.4, U1.4 (GP2), U6.6 (A4)
/P_S3_BUSY: J10.12, U1.12 (GP9), U6.7 (A5)
/P_S3_CS_N: J10.17, R16.2, U1.17 (GP13), U5.7 (A5)
/P_S3_IRQ: J10.11, U1.11 (GP8), U6.8 (A6)
/P_S4_BUSY: J10.15, U1.15 (GP11), U6.9 (A7)
/P_S4_CS_N: J10.19, R17.2, U1.19 (GP14), U5.8 (A6)
/P_S4_IRQ: J10.14, U1.14 (GP10), U6.10 (A8)
/P_SPI_MISO: J10.6, TP46.1, U1.6 (GP4), U7.3 (A)
/P_SPI_MOSI: J10.10, TP45.1, U1.10 (GP7), U5.4 (A2)
/P_SPI_SCK: J10.9, TP44.1, U1.9 (GP6), U5.3 (A1)
/RADIO_5V: C3.1 (+), C4.1, J1.2, J1.3, J3.2, J3.3, J5.2, J5.3, J7.2, J7.3, Q1.3 (D), R11.1, TP1.1, TP9.1, TP15.1, TP23.1, TP32.1, U2.6 (OUT), U3.1 (VIN), U3.3 (EN)
/S1_BUSY: J2.1, TP3.1, U6.21 (B1)
/S1_CS_N: J1.8, TP2.1, U5.19 (B3)
/S1_IRQ: J2.2, TP4.1, U6.20 (B2)
/S1_RESET_N: J1.9, TP5.1, U4.1 (GPB0)
/S1_RX_EN: J2.4, TP7.1, U4.22 (GPA1)
/S1_TX_EN: J2.3, TP6.1, U4.21 (GPA0)
/S2_BUSY: J4.1, TP11.1, U6.19 (B3)
/S2_CS_N: J3.8, TP10.1, U5.18 (B4)
/S2_IRQ: J4.2, TP12.1, U6.18 (B4)
/S2_RESET_N: J3.9, TP13.1, U4.2 (GPB1)
/S3_BUSY: J6.1, TP17.1, U6.17 (B5)
/S3_CS_N: J5.8, TP16.1, U5.17 (B5)
/S3_IRQ: J6.2, TP18.1, U6.16 (B6)
/S3_RESET_N: J5.9, TP19.1, U4.3 (GPB2)
/S3_RX_EN: J6.4, TP21.1, U4.24 (GPA3)
/S3_TX_EN: J6.3, TP20.1, U4.23 (GPA2)
/S4_BUSY: J8.1, TP25.1, U6.15 (B7)
/S4_CS_N: J7.8, TP24.1, U5.16 (B6)
/S4_IRQ: J8.2, TP26.1, U6.14 (B8)
/S4_RESET_N: J7.9, TP27.1, U4.4 (GPB3)
/S4_RX_EN: J8.4, TP29.1, U4.26 (GPA5)
/S4_TX_EN: J8.3, TP28.1, U4.25 (GPA4)
/SPI_MISO: J1.7, J3.7, J5.7, J7.7, R10.1, R22.2, TP49.1, U7.4 (B)
/SPI_MOSI: J1.6, J3.6, J5.6, J7.6, R21.2, TP48.1, U4.13 (SI)
/SPI_MOSI_SRC: R21.1, U5.20 (B2)
/SPI_SCK: J1.5, J3.5, J5.5, J7.5, R20.2, TP47.1, U4.12 (SCK)
/SPI_SCK_SRC: R20.1, U5.21 (B1)
/USB_VBUS: J11.20, Q1.1 (G), R7.1, TP33.1, U1.40 (VBUS)
/UVLO: R1.2, R2.1, TP37.1, U2.1 (EN_UVLO)

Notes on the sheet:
R20/R21: immediately after U5 SCK/MOSI outputs. R22: at U4 SO before shared MISO. 22R initial; 0R population option. Verify by oscilloscope/IBIS. No long stubs. Each radio card has its own MISO source resistor before slot A7.
18/26 GPIO used; eight spare including GP26-28, all physically NC. BUSY/IRQ/CS are direct GPIO through fixed-direction isolation, not expander GPIO. KEY: captive M3 x 25 alignment post, see radio-slot-v0.1.md. U4 GPA0..5 = S1/S3/S4 TX,RX pairs; GPB0..3 = S1..4 RESET_N. No autonomous duty-cycled RX 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
USB-only: Q1 off; RADIO_5V and IOREF_3V3 unpowered. External power: U2 -> radios and Q1 -> VSYS. Q1 orientation is intentional: body diode from RADIO_5V toward VSYS. Pico onboard D1 blocks USB backfeed. #FLG01/#FLG02 model the external supply; #FLG03 models real Q1/onboard USB-D1 ORing output. U2 A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
REV A LAYOUT REVIEW. NOT FOR FABRICATION.
Four-slot carrier: protected external 5 V / 4 A, isolated GPIO
Local labels connect equal names. NC marks deliberate unused module pins. Selected parts: see BOM, FOOTPRINT_REVIEW.md and ASSEMBLY_NOTES.md.
